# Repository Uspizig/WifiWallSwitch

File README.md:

A WallSwitch with a clever EINK Display that measures your Air Quality, measures Temperature, detects movement, measures Light Conditions... and many more.
And the Best of all: "It can be your own LOCAL Voice Assistant or MediaPlayer"

This Device perfectly integrates in your Smart Home (e.g. HomeAssistant or IO Broker).  
No permanent backlight On Display that disturbs your sleep. Just a brillant E-Ink Display with outstanding contrast and some Buttons that you can feel when you swipe over with your plam.
A lightweight Design with a perfect WAF Factor. Fits on your Desktop or on your wall. 
The device can be programmed, adapted, hacked, tinkered and individualised by YOU.
You want to push boundries even further: Use Arduino and do a deep Dive in Ultra Low Power Mode. The Battery might run for Years with an intelligent Power Gateing.

Eight Ambient Light LEDs can give you a visual quick feedback if needed:

View of the components in HomeAssistant

What is under the hood:
Main thing you see when you have a first look is the massive 2.7 " E-Ink Screen

See it in Action here: https://twitter.com/USpizig/status/1747731234338336940

Hardware Specs:
- 2.7" EInk Epaper with or without Touch Screen... other screens might work as well
- ESP32 S3 Dual Core Microcontroller with USB OTG, Wifi & BT, Mass Storage Mode. 
- 8 X SK6812 Mini RBG LEDs
- 8 X Hardware Buttons...REAL BUTTONS with clicks: No Touch Buttons that might not work if you have wet or dirty fingers
- BOSCH BME680 for eCo2, Temperature, Humidity and Pressure Measurements
- ST LSM6DSL Ultra Low Noise MEMS Gyro + Accel for Movement Detection and Earthquake Detection
- INMP441 MEMS Microphone for Voice Assistant
- Socket for MAX98357A I2S Class D Amplifier for Audio Output for Media Player
- LDR Ambient Light Sensor: Detect the Ambient Light conditions in your room.
- RTC1: TPL5110 for PowerGateing and low Standby Current
- RTC2 Option: RV3028 C7 for Ultra Low RTC with Backup Cap lasts 3h
- Optional: RFM95 LoRa Radio for Desaster Radio (Limitations: May not work together with Microphone)
- Connector for KNX EIB Smart Home with Nano BCU
- Connector for Your Own Ideas... Several free GPIOs
- Switch for adapting to Waveshare/Gooddisplay EINK Display
- All SMD components have a size 0603 or larger to enable easier soldering/Tinkering.

Underneath the EINK Screen is a placeholder for an optional RFM95/RFM98 Long Range Communication Module. This Module works with LoRa, FSK or other wireless standards. 
Up 15km Range of communication can be established with this module. Perfect as well for decoding your Bresser Weather Station and translate it to MQTT for your Smart Home.

The other side of the PCB looks like this:

If you scroll further down you may see a picture of the TOP View of the PCB
On the Top side of the PCB you see the Main Processor: This is an ESP32-S3 and various sensors:
- Ultra Low Power RTC RV3028 [U9] for Low Power Battery Operation wakeup
- Ultra Low Noise MEMS LSM6DSL [U8] 6 Axis GYRO+ACCEL + Tap Detection
- Ultra Low Power Gateing Chip TPL5110: [U6]
- Bosch BME680 for Air Quality Measurements [U5]
- EInk Screen connector 
- Touch Screen connector [JP5]
- Space for the oprional INMP441 Microphone [J5], [J9]
- 8 RGB LEDs which can be adressed individually. Perfect for Quizshow effects. Ideal for Audiovisual feeddback
- 9 Click Buttons. [SW1-SW9] - SW5 is hidden under the screen and can be used as Physical Click Button
- Space for Several Connectors[J2, J8, J3] to plugin even more modules like Audio Module for an Media Player or Voice Assistant Feedback.

And another view with all the SMD Parts simulated:

What is currently working:

Hardware:
- Currently the HW BringUp is about to finish.
- The basic Hardware is up and running stable.
- Eink, Microphone, LEDs, Buttons, BME680. LSM6 Gyro work well.

The optional Modules are  still under test
  -   TP4065 Lipo Battery Charger Circuit
  -   Battery Switchover Circuit once Battery is fully charged to avoid Battery damage due to overcharging
  -   TPL5110 Low Power RTC Module
  -   RV3028 Low Power Module
  -   Long Range Communication Module RF Module RFM95
  -   230V Power Converter to 5V/3.3V for Wall Mode.

Software Sketches working:
Arduino:
  - Flashing the Device over USB with you Chrome Web Browser: https://web.esphome.io/
  - Logging over USB USBSerial
  - EInk Basic Update of content
  - EInk Partial Update Dynamic Update of content
  - Read out BME680 Data (Temp, Humidity, Pressure, eCO2, IAQ,...)
  - Microfone: Calculate loudness in dBA
  - Audio Player: Playback MP3, TTS via Google and Webradio
  - 8 Buttons can be detected.
  - 8 RGB LEDS whcih can be adressed individually
  - LSM6 Gyro: Read out of Basic Values Roll, Pitch, Yaw
  - All typical 24pin EInk Displays which are mentioned on GxEPD2: https://github.com/ZinggJM/GxEPD2/tree/master
  - Flashing & Logging the Device over 2.54mm Socket with a dedicated Flash Adapter

 Home Assistant with ESPHome Integration:
   - Flashing the Device over USB with you Chrome Web Browser: https://web.esphome.io/
   - Logging over USB with ESP Home
   - Display Messages on EInk Display
   - Voice Assistant: Switch on Light,.... you name it
   - Media Player: Playback of TTS Messages, Audio Files,Web Radio
   - Keyboard: 8 Buttons are detected individulally
   - RGB LED Control SK6812 Mini
   - Flashing & Logging the Device over 2.54mm Socket with a dedicated Flash Adapter
     
Known ESPHome Issues right now:
  - Voice Assistant has some issues if used together with Media Player. Leads to Stuttering Audio once Media Playback is started.
  - No LSM GYRO integration
  - 2 GPIOS used to much due to Keypad component of ESPhome only supports 4x4 Matrix Keyboards
  - GPIO8 can not be used for Keyboard Fake Keys.

Known Issues on Arduino:
  - LSM6 Gyro has some issues with BME680 BSEC: Leads to constant output of 500 ppm

What is planned:
- EInk Touch Screen 2.7 'integration of Good Display https://www.good-display.com/product/259.html
- A Touch screen https://www.good-display.com/product/259.html
- Read out data of a Weather Station Bresser 6in1 We<ther Station and forward to MQTT with an RFM95 Chip.
- LDR for Light Detection. Monitoring of Enviroment Data
- Ultra Low Power RTC RV3028 for Low Power Battery Operation wakeup
- Ultra Low Noise MEMS LSM6DSL GYRO+ACCEL for Earthquake Detection-> https://github.com/biagiom/QuakeSense
- Ultra Low Noise MEMS LSM6DSL for movement detection and Tap Detection
- Ultra Low Power Mode TPL5110: Let the Processor sleep with TPL5110 Power Gateing and shut down all that is battery draining.
- Bosch BME680 for Air Quality Measurements
- 9 physical buttons for moments where you do not wnat to use a touchscreen
- KNX Integraion with Nano BCU
- LORA:
  - Transmit Air Quality Data on a regular Basis (every 15min)
  - Transmit Data when Air Quality changes dramatically
  - Transmit Data when Air Quality changes dramatically
  - Recieve Commands to Switch on / off ext Relay
  - Switch to Desaster Mode and search for BLE Heart Rate Devices nearby and sent this data via LoRa

WARNINGS
This is my hobby. Please do NOT be a DIRTY COPY CAT and make your own comercial product out of it.
See License before you copy anything out of it.
 
If you use this Hardware, Software, Code or schematics you agree that any harm, damage, burn or injuries are YOUR RESPONSIBILITY! 
The Author may not be held liable for any damage that might happen if you try this code out or use this product or parts of it.
Legal validity of this disclaimer: This disclaimer is to be regarded as part of the internet publication which you were referred from. 
If sections or individual terms of this statement are not legal or correct, the content or validity of the other parts remain uninfluenced by this fact.

Referrals and links The author is not responsible for any contents linked or referred to from his pages - unless he has full knowledge of illegal contents and would be able to prevent the visitors of his site from viewing those pages. If any damage occurs by the use of information presented there, the author might not be liable. Furthermore the author is not liable for any postings or messages published by users of discussion boards, guest books or mailing lists provided.

Arduino:
Before you compile please ensure you modify all your credentials and used sensors in "credentials.h" which have been marked REPLACEMEUSER
This Source Code is provided "AS it is" . 
Also ensure you have installed the following libs:
Code Sources that influenced this Source Code and which libaries you may need:

https://github.com/knolleary/pubsubclient/blob/master/examples/mqtt_auth/mqtt_auth.ino
https://randomnerdtutorials.com/esp32-mqtt-publish-subscribe-arduino-ide/
RGBW for SK6812:
Original code by Jim Bumgardner (http://krazydad.com).
Modified by David Madison (http://partsnotincluded.com).
Extended by Christoph Wempe
https://gist.github.com/CWempe?direction=desc&sort=created

Adafruit BME/BMP280/SGP30 sketches/libs
Please consider buying their products due to their great work in Arduino libs
https://github.com/adafruit/Adafruit_SGP30
https://github.com/adafruit/Adafruit_BMP280_Library

Bosch BME680 BSEC Lib
https://github.com/BoschSensortec/BSEC-Arduino-library

Andreas Spiess
OTA Sketch for OTA Update of the ESP32 over Wifi
https://github.com/SensorsIot/ESP32-OTA

Knolleary pubsubclient
/pubsubclient/blob/master/examples/mqtt_auth/mqtt_auth
https://github.com/knolleary/pubsubclient

Fastled
https://github.com/FastLED/FastLED

Settings for Jumpers & Solder Bridges:
Jumper:
- JP2 = This MUST BE OPEN! if USB Connected & 3.3V Prog
- JP3 = GYRO INT Emergency CUT: If you want no more Interupts from the Gyro.
- JP4 = MAINS Mode / No TPL5110 Mode. Disable the RTC for Power Gateing. Use for permanent connection to USB
- JP5 = RV3028 INT CUT for RFM95 OP. Must be cut if an RFM Long Range RF Mode is installed
- JP6 = Switch of Input Power Supply Voltage
- JP5 = Solder for RFM95 OP & Cut JP5

I²C Address of onboard Devices.
- 0x52 RV3028
- 0x6A LSM6DSL
- 0x77 BME680

Testpoints for soldering and Tinkering:
TP1 EPD VCOM -> Debuging of EINK
TP2 CLK RV3028 
TP3 INT RV3028
TP4 EPD PREVGL -> Debuging of EINK
TP5 EPD PREVGH -> Debuging of EINK
TP6 TPL DNE -> Debuging of EINK... Connect to a GPIO for Ulatra Low Power sleep and fire a 1 whenever you want to Deep Sleep on that GPIO
TP7 SHOT RV3028 -> Wakeup Pin for RTC2
TP8 RFM CS -> Soldering Pin needed for RFM95
TP9 JTAG/Done
TP10 RFM ANT -> Connector for 868 MHZ Antenna
TP11 TPL SHOT -> Wakeup Pin for TPL 5110 RTC
TP12 GYRO INT2
TP13 GYRO INT1
TP14 TOUCH RES -> Touch Controller Reset Pin. Hopefully never needed
TP15 BAT CHRG -> Battery charg Pin. Hopefully never needed.

Known HW Limitations:
- LDR is not working when WIFI is ON. Stupid ESP32-S3 Limitations ADC2 is not working if WIFi is on
- HW Buttons placed 90° wrong. Wrong Pinout matching

TODO:
- RV_3028 INT ist connected with LORA RFM MISO. No paralell usage possible
- INMP441 Mic ist connected with LORA RFM95. No paralell usage possible
- USB ESD Diodes missing
- SK6812 is an input of KNX connector at the same time?
- Rerouting of SK6812 necesssary. Not possible to  GPIO 0... otherwise board will not start.
- Done Pin TPL5110 not routed to ESP32 IO3. No Power Shutdown without a Solder Bridge
-

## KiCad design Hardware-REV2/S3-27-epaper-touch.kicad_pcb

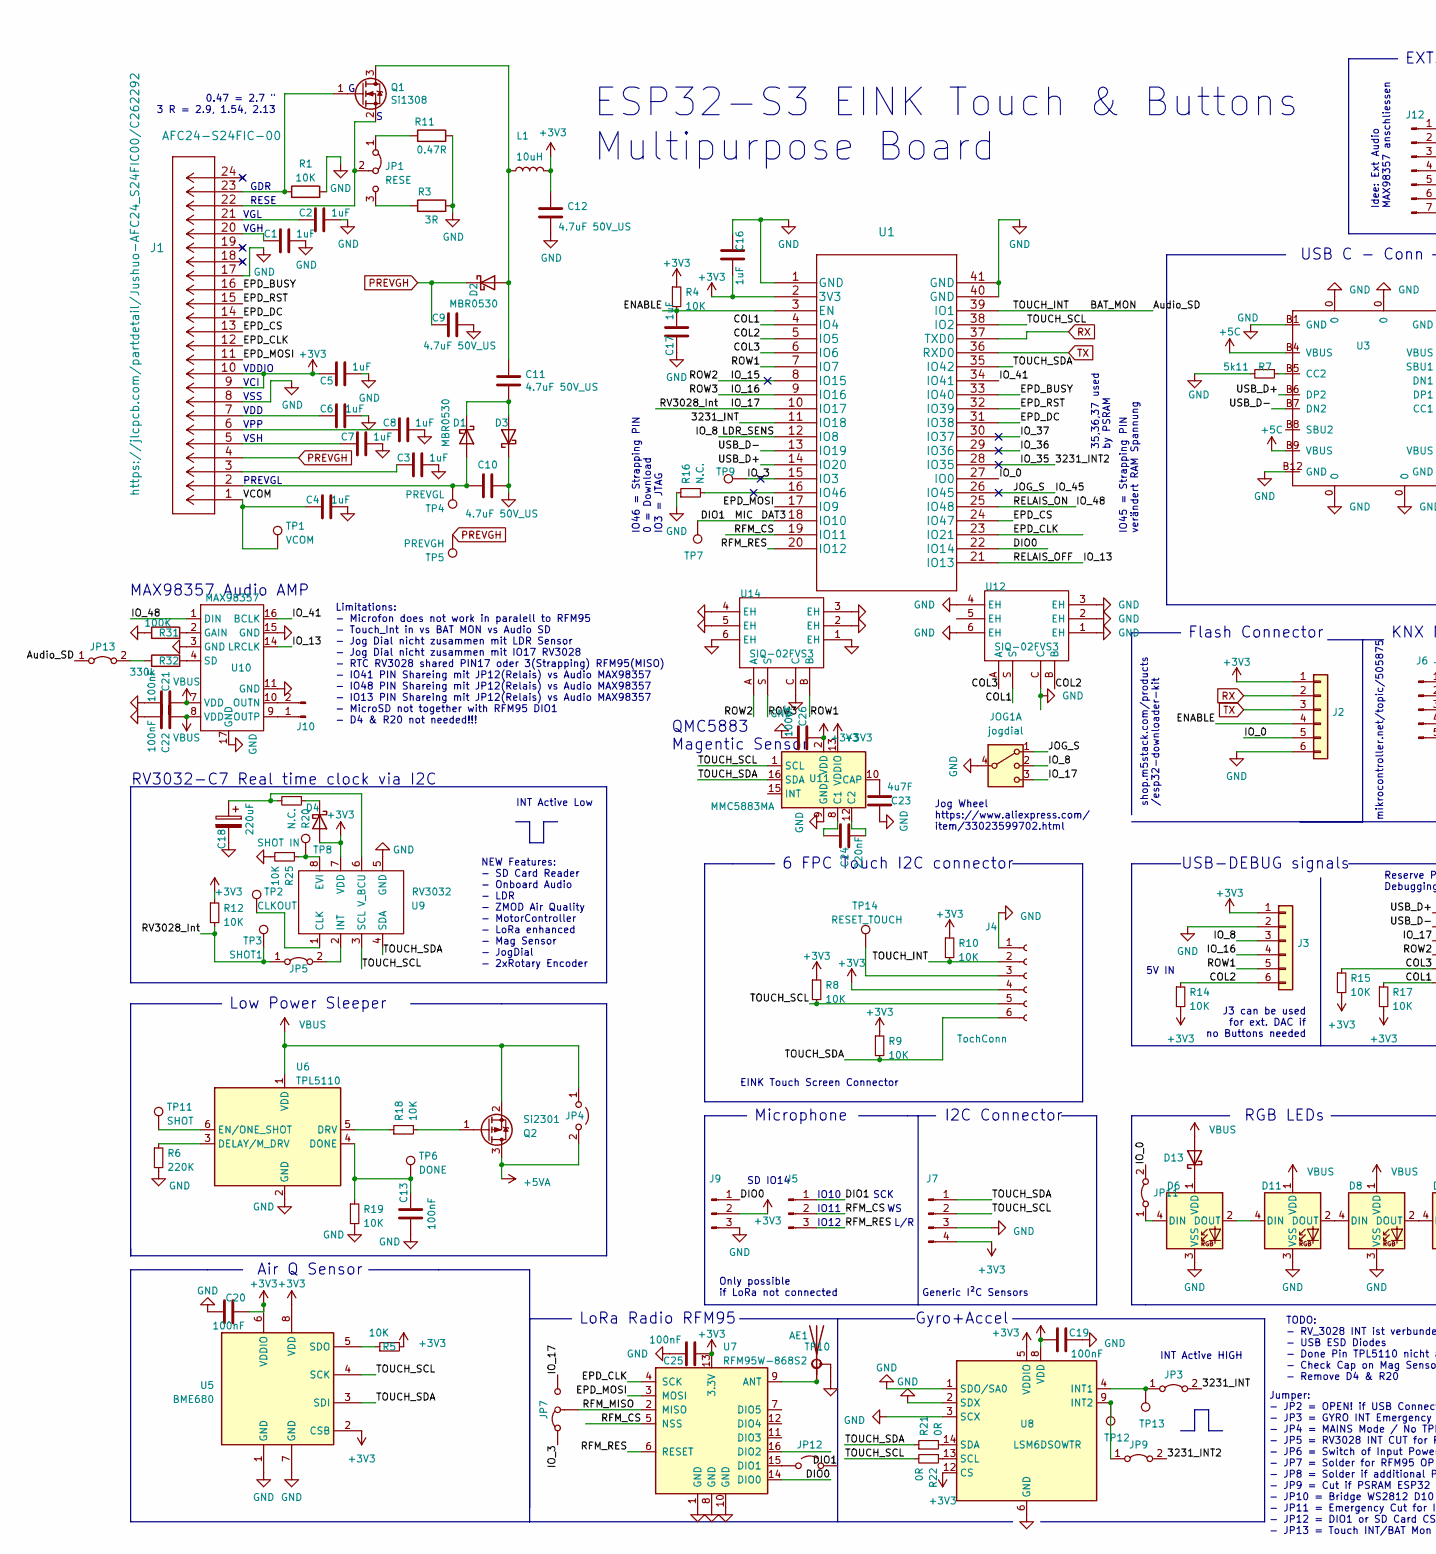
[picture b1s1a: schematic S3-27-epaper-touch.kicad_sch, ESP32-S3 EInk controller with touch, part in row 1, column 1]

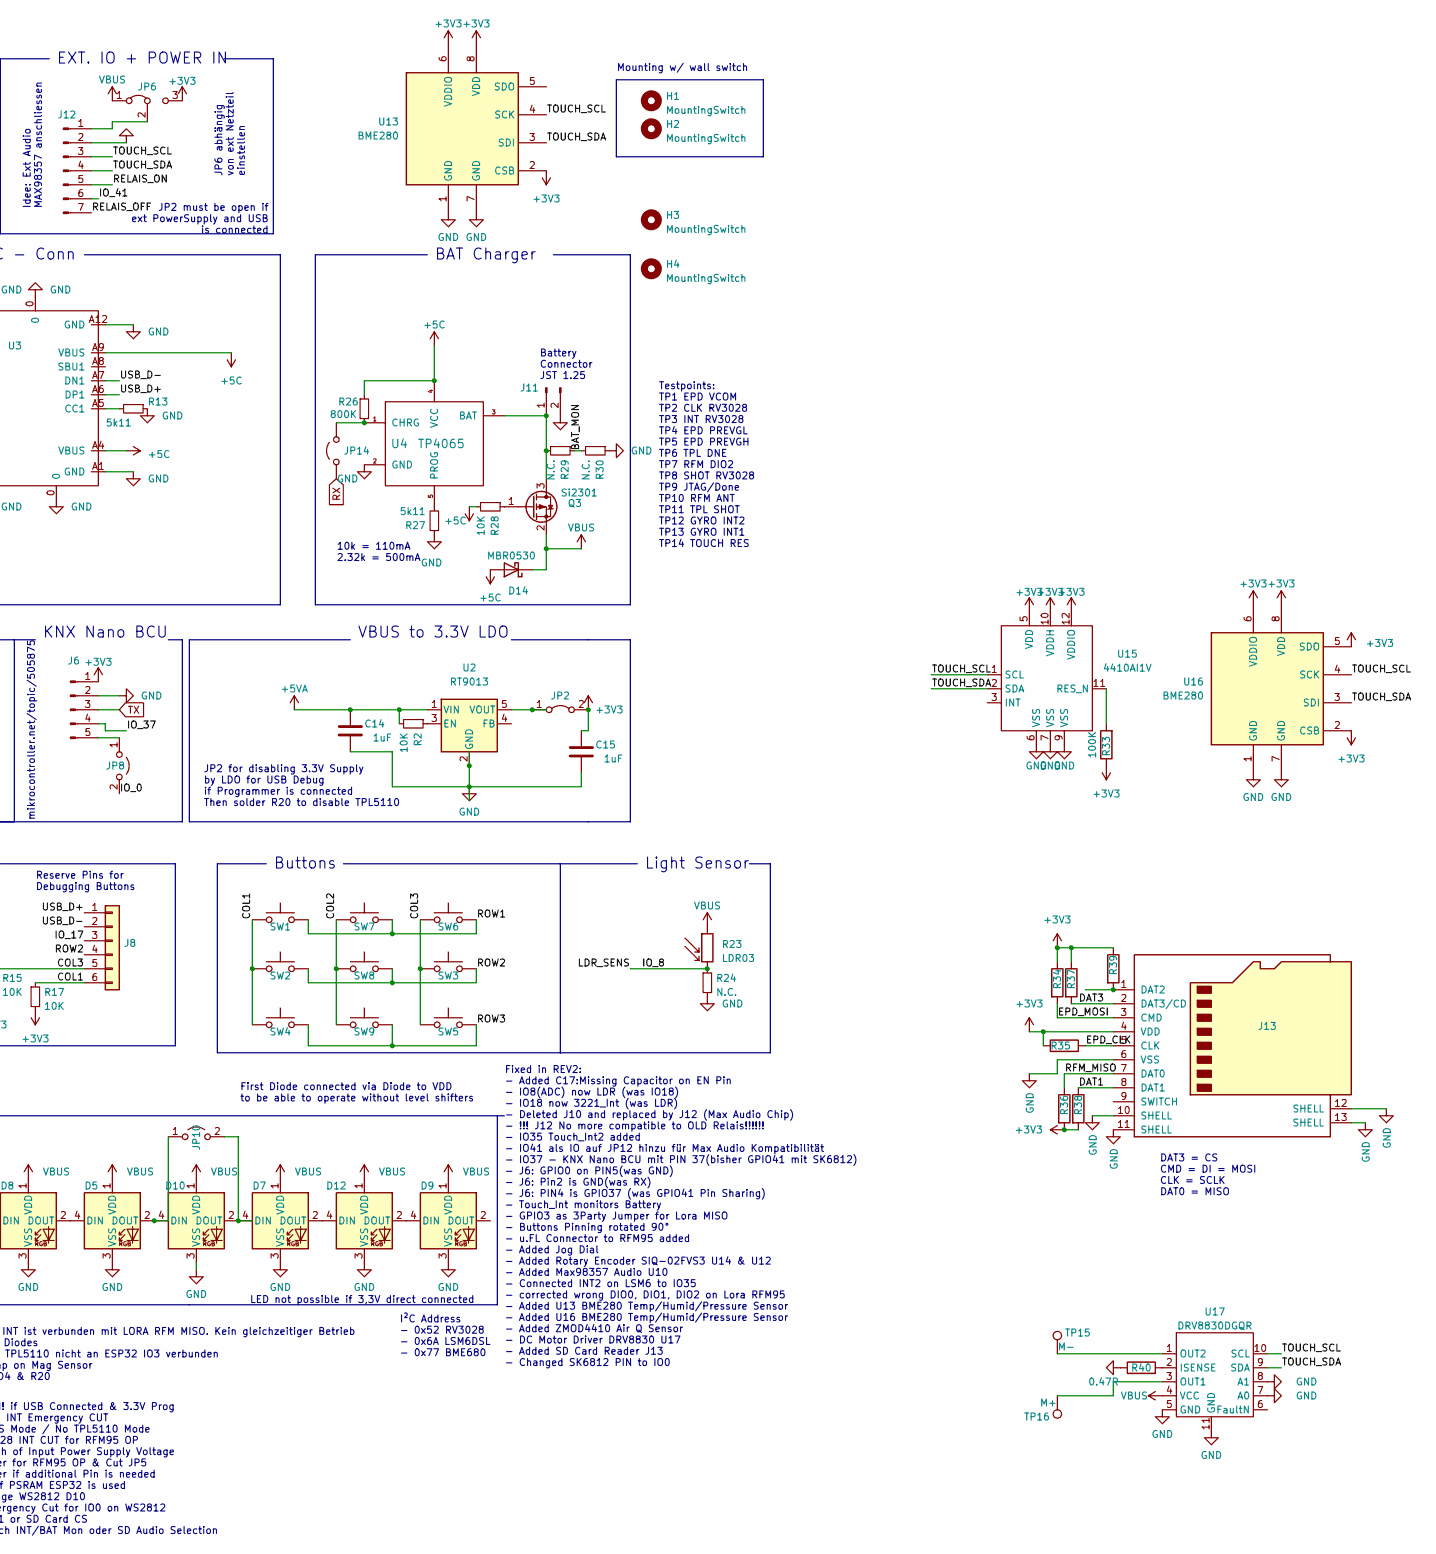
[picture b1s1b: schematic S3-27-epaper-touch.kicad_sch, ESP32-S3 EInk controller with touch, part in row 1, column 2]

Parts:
AE1: Antenna_Shield; U.FL_Molex_MCRF_73412-0110_Vertical
C1, C2, C3, C4, C5, C6, C7, C8, C14, C15, C16, C17: 1uF; C_0805_2012Metric_Pad1.18x1.45mm_HandSolder; LCSC C28323
C9, C10, C11, C12: 4.7uF 50V_US; C_0805_2012Metric_Pad1.18x1.45mm_HandSolder; LCSC C162420
C13, C19, C20: 100nF; C_0805_2012Metric_Pad1.18x1.45mm_HandSolder; LCSC C49678
C18: 220uF; CP_EIA-3528-21_Kemet-B
C21, C22, C26: 100nF; C_0805_2012Metric_Pad1.18x1.45mm_HandSolder
C23: 4u7F; C_0805_2012Metric_Pad1.18x1.45mm_HandSolder
C24: 220nF; C_0805_2012Metric_Pad1.18x1.45mm_HandSolder
C25: 100nF; C_0603_1608Metric_Pad1.08x0.95mm_HandSolder
D1, D2, D3, D4, D13, D14: MBR0530; D_SOD-123
D5, D6, D7, D8, D9, D10, D11, D12: SK6812MINI-E; MX_SK6812MINI-E
H1, H2: MountingSwitch; MountingHole_3.2mm_M3
H3, H4: MountingSwitch; baerklein
J1: AFC24-S24FIC-00; FPC-SMD_P0.50-24P_QCHF-SM-H2.0; LCSC C262292
J2, J3, J8: Conn_01x06; PinHeader_1x06_P2.54mm_Vertical
J4: TochConn; FFC-SMD_6P-P0.50_FH34SRJ-6S-0.5SH; LCSC C224194
J5, J9: Conn_01x03_Pin; PinHeader_1x03_P2.54mm_Vertical
J6: Conn_01x05_Pin; PinHeader_1x05_P2.54mm_Vertical
J7: Conn_01x04_Pin; PinHeader_1x04_P2.54mm_Vertical
J10: Conn_01x02_Pin; PinHeader_1x02_P2.00mm_Vertical
J11: Conn_01x02_Pin; JST_GH_SM02B-GHS-TB_1x02-1MP_P1.25mm_Horizontal
J12: Conn_01x07_Pin; PinHeader_1x07_P2.54mm_Vertical
J13: Micro_SD_Card_Det_US; TF-SMD_XKTF-0803-0
JOG1: jogdial; JogWheel
JP1: RESE; SW-SMD_G-SWITCH_MK-12C02-G015; LCSC C2911519
JP2, JP3, JP5, JP11: Jumper_2_Bridged; SolderJumper-2_P1.3mm_Bridged_RoundedPad1.0x1.5mm
JP4, JP8, JP12, JP14: Jumper_2_Open; SolderJumper-2_P1.3mm_Open_RoundedPad1.0x1.5mm
JP6, JP7: Jumper_3_Bridged12; SolderJumper-3_P1.3mm_Bridged12_RoundedPad1.0x1.5mm_NumberL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
JP9, JP13: Jumper_2_Bridged; SolderJumper-2_P1.3mm_Open_RoundedPad1.0x1.5mm
JP10: Jumper_2_Open; SolderJumper-2_P1.3mm_Bridged_RoundedPad1.0x1.5mm
L1: 10uH; IND-SMD_L4.0-W4.0
Q1: Si1308; SOT-323_SC-70
Q2, Q3: Si2301; SOT-23
R1, R2, R4, R5, R8, R9, R10, R12, R14, R15, R17, R18, R19, R25, R28: 10K; R_0805_2012Metric_Pad1.20x1.40mm_HandSolder; LCSC C17414
R3: 3R; R_0805_2012Metric_Pad1.20x1.40mm_HandSolder
R6: 220K; R_0805_2012Metric_Pad1.20x1.40mm_HandSolder
R7, R13, R27: 5k11; R_0805_2012Metric_Pad1.20x1.40mm_HandSolder; LCSC C27834
R11, R40: 0.47R; R_0805_2012Metric_Pad1.20x1.40mm_HandSolder
R16, R24, R29, R30: N.C.; R_0603_1608Metric_Pad0.98x0.95mm_HandSolder
R20: N.C.; R_0805_2012Metric_Pad1.20x1.40mm_HandSolder
R21, R22: 0R; R_0805_2012Metric_Pad1.20x1.40mm_HandSolder; LCSC C17477
R23: LDR03; R_LDR_10x8.5mm_P7.6mm_Vertical
R26: 800K; R_0805_2012Metric_Pad1.20x1.40mm_HandSolder
R31: 100K; R_0805_2012Metric_Pad1.20x1.40mm_HandSolder
R32: 330k; R_0805_2012Metric_Pad1.20x1.40mm_HandSolder
R33: 100K; R_0603_1608Metric_Pad0.98x0.95mm_HandSolder
R34, R35, R36, R37, R38, R39: 10k; R_0603_1608Metric_Pad0.98x0.95mm_HandSolder
SW1, SW2, SW3, SW4, SW5, SW6, SW7, SW8, SW9: SW_Push; SW-SMD_4P-CORR-L5.2-W5.2-P3.70-LS6.4
TP1, TP7, TP9, TP13: VCOM; TestPoint_Pad_D1.5mm
TP2: CLKOUT; TestPoint_Pad_D1.5mm
TP3: SHOT1; TestPoint_Pad_D1.5mm
TP4: PREVGL; TestPoint_Pad_D1.5mm
TP5: PREVGH; TestPoint_Pad_D1.5mm
TP6: DONE; TestPoint_Pad_D1.5mm
TP8: SHOT IN; TestPoint_Pad_D1.5mm
TP10: VCOM; PinHeader_1x01_P2.54mm_Vertical
TP11: SHOT; TestPoint_Pad_D1.5mm
TP12: VCOM; TestPoint_Pad_D1.0mm
TP14: RESET_TOUCH; TestPoint_Pad_D1.5mm
TP15: M-; TestPoint_Pad_D1.0mm
TP16: M+; TestPoint_Pad_D1.0mm
U1: ESP32-S3-WROOM-1-N8; ESP32-S3-WROOM-1
U2: RT9013; SOT-23-5; LCSC C47773
U3: KoreanHropartsElecTYPE-C-31-M-12; USB-C_SMD-TYPE-C-31-M-12; LCSC C165948
U4: TP4065; SOT-23-5_L3.0-W1.7-P0.95-LS2.8-BR; LCSC C113540
U5: BME680; LGA-8_L3.0-W3.0-P0.80-TR; LCSC C125972
U6: TPL5110; SOT-23-6; LCSC C125830
U7: RFM95W-868S2; HOPERF_RFM9XW_SMD; LCSC C2844472
U8: LSM6DSOWTR; LGA-14_3x2.5mm_P0.5mm_LayoutBorder3x4y; LCSC C2829074
U9: RV3032; rv3028
U10: MAX98357; TQFN-16_L3.0-W3.0-P0.50-BL-EP1.5
U11: MMC5883MA; LGA-16_3x3mm_P0.5mm
U12, U14: SIQ-02FVS3; SW-SMD_SIQ-02FVS3_1; Manufacturer Part SIQ-02FVS3; LCSC Part Name 拨轮滚轮旋转编码器开关
U13, U16: BME280; Bosch_LGA-8_2.5x2.5mm_P0.65mm_ClockwisePinNumbering
U15: 4410AI1V; ZMOD4410AI1V
U17: DRV8830DGQR; HVSSOP-10-1EP_3x3mm_P0.5mm_EP1.57x1.88mm

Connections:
+3V3: C5.2, C12.2, C15.1, C16.1, C19.2, C20.2, C25.2, C26.1, D4.2 (A), J1.9, J1.10, J2.1, J3.1, J4.4, J6.1, J7.4, J9.2, J13.4 (VDD), JP2.2 (B), JP6.3 (B), L1.2, R4.1, R5.2, R8.1, R9.1, R10.1, R12.1, R14.2, R15.2, R17.2, R33.1, R34.1, R35.1, R36.2, R37.1, R38.2, R39.1, U1.2 (3V3), U5.2 (CSB), U5.6 (VDDIO), U5.8 (VDD), U7.13 (3.3V), U8.5 (VDDIO), U8.8 (VDD), U8.12 (CS), U9.7 (VDD), U11.2 (VDD), U11.13 (VDDIO), U13.2 (CSB), U13.6 (VDDIO), U13.8 (VDD), U15.5 (VDD), U15.10 (VDDH), U15.12 (VDDIO), U16.2 (CSB), U16.5 (SDO), U16.6 (VDDIO), U16.8 (VDD)
+5C: D14.2 (A), R26.1, R28.2, U3.A4 (VBUS), U3.A9 (VBUS), U3.B4 (VBUS), U3.B9 (VBUS), U4.4 (VCC)
+5VA: C14.1, JP4.2 (B), Q2.3 (D), R2.2, U2.1 (VIN)
/3231_INT: JP3.2 (B), U1.11 (IO18)
/3231_INT2: JP9.2 (B), U1.28 (IO35)
/Audio_SD: J4.2, JP13.1 (A), R10.2, R29.1, R30.2, U1.39 (IO1)
/COL1: J8.6, R17.1, SW1.1, SW2.1, SW4.1, U1.4 (IO4), U12.S
/COL2: J3.6, R14.1, SW7.1, SW8.1, SW9.1, U1.5 (IO5), U12.B
/COL3: J8.5, R15.1, SW3.1, SW5.1, SW6.1, U1.6 (IO6), U12.A
/DAT1: J13.8 (DAT1), R38.1
/DAT3: J5.1, J13.2 (DAT3/CD), JP12.2 (B), R37.2, TP7.1, U1.18 (IO10)
/DIO0: J9.1, U1.22 (IO14), U7.14 (DIO0)
/ENABLE: C17.1, J2.4, R4.2, U1.3 (EN)
/EPD_BUSY: J1.16, U1.33 (IO40)
/EPD_CLK: J1.12, J13.5 (CLK), R35.2, U1.23 (IO21), U7.4 (SCK)
/EPD_CS: J1.13, U1.24 (IO47)
/EPD_DC: J1.14, U1.31 (IO38)
/EPD_MOSI: J1.11, J13.3 (CMD), R34.2, U1.17 (IO9), U7.3 (MOSI)
/EPD_RST: J1.15, U1.32 (IO39)
/IO_0: J2.5, JP8.2 (B), JP11.2 (B), U1.27 (IO0)
/IO_3: JP7.1 (A), TP9.1, U1.15 (IO3)
/IO_8: J3.3, JOG1.2, R23.2, R24.1, U1.12 (IO8); also elsewhere on the board
/IO_13: J12.7, U1.21 (IO13), U10.14 (LRCLK)
/IO_15: J8.4, SW2.2, SW3.2, SW8.2, U1.8 (IO15), U14.A
/IO_16: J3.4, SW4.2, SW5.2, SW9.2, U1.9 (IO16), U14.S
/IO_17: J8.3, JOG1.3, JP5.1 (A), JP7.3 (B), R12.2, TP3.1, U1.10 (IO17); also elsewhere on the board
/IO_36: U1.29 (IO36)
/IO_37: J6.4, U1.30 (IO37)
/IO_41: J12.6, U1.34 (IO41), U10.16 (BCLK)
/IO_45: JOG1.1, U1.26 (IO45); also elsewhere on the board
/IO_48: J12.5, U1.25 (IO48), U10.1 (DIN)
/RFM_CS: J5.2, U1.19 (IO11), U7.5 (NSS)
/RFM_MISO: J13.7 (DAT0), JP7.2 (C), R36.1, U7.2 (MISO)
/RFM_RES: J5.3, U1.20 (IO12), U7.6 (RESET)
/ROW1: J3.5, SW1.2, SW6.2, SW7.2, U1.7 (IO7), U14.B
/TOUCH_SCL: J4.5, J7.2, J12.3, R8.2, R22.2, U1.38 (IO2), U5.4 (SCK), U9.3 (SCL), U11.1 (SCL), U13.4 (SCK), U15.1 (SCL), U16.4 (SCK), U17.10 (SCL)
/TOUCH_SDA: J4.6, J7.1, J12.4, R9.2, R21.1, U1.35 (IO42), U5.3 (SDI), U9.4 (SDA), U11.16 (SDA), U13.3 (SDI), U15.2 (SDA), U16.3 (SDI), U17.9 (SDA)
/USB_D+: J8.1, U1.14 (IO20), U3.A6 (DP1), U3.B6 (DP2)
/USB_D-: J8.2, U1.13 (IO19), U3.A7 (DN1), U3.B7 (DN2)
/VCOM: C4.2, J1.1, TP1.1
GND: AE1.2 (Shield), C1.1, C2.1, C3.1, C4.1, C5.1, C6.1, C7.1, C8.1, C9.1, C10.1, C12.1, C13.2, C14.2, C15.2, C16.2, C17.2, C18.2, C19.1, C20.1, C21.2, C22.2, C23.1, C25.1, C26.2, D3.1 (K), D5.3 (VSS), D6.3 (VSS), D7.3 (VSS), D8.3 (VSS), D9.3 (VSS), D10.3 (VSS), D11.3 (VSS), D12.3 (VSS), J1.8, J1.17, J2.6, J3.2, J4.1, J6.2, J7.3, J9.3, J11.2, J12.2, J13.6 (VSS), J13.10 (SHELL), J13.11 (SHELL), J13.12 (SHELL), J13.13 (SHELL), JOG1.4, R1.2, R3.2, R6.2, R7.2, R11.2, R13.1, R16.1, R19.2, R24.2, R25.2, R27.1, R30.1, R31.1, R40.1, U1.1 (GND), U1.40 (GND), U1.41 (GND), U2.2 (GND), U3.0, U3.A1 (GND), U3.A12 (GND), U3.B1 (GND), U3.B12 (GND), U4.2 (GND), U5.1 (GND), U5.7 (GND), U6.2 (GND), U7.1 (GND), U7.8 (GND), U7.10 (GND), U8.1 (SDO/SA0), U8.2 (SDX), U8.3 (SCX), U8.6 (GND), U8.7 (GND), U9.5 (GND), U10.3 (GND), U10.11 (GND), U10.15 (GND), U10.17 (GND), U11.9 (GND), U11.11 (GND), U12.1 (EH), U12.2 (EH), U12.3 (EH), U12.4 (EH), U12.6 (EH), U12.C, U13.1 (GND), U13.7 (GND), U14.1 (EH), U14.2 (EH), U14.3 (EH), U14.4 (EH), U14.5 (EH), U14.6 (EH), U14.C, U15.6 (VSS), U15.7 (VSS), U15.9 (VSS), U16.1 (GND), U16.7 (GND), U17.5 (GND), U17.7 (A0), U17.8 (A1), U17.11 (GND); also elsewhere on the board
unnamed: AE1.1 (A), TP10.1, U7.9 (ANT)
unnamed: C1.2, J1.20
unnamed: C2.2, J1.21
unnamed: C3.2, J1.3
unnamed: C6.2, J1.7
unnamed: C7.2, J1.5
unnamed: C8.2, J1.6
unnamed: C10.2, D1.2 (A), J1.2, TP4.1
unnamed: C11.1, D1.1 (K), D3.2 (A)
unnamed: C11.2, D2.2 (A), L1.1, Q1.3 (D)
unnamed: D4.1 (K), R20.1
unnamed: D5.4 (DIN), D8.2 (DOUT)
unnamed: D6.4 (DIN), JP11.1 (A)
unnamed: D5.2 (DOUT), D10.4 (DIN), JP10.1 (A)
unnamed: D7.4 (DIN), D10.2 (DOUT), JP10.2 (B)
unnamed: D6.2 (DOUT), D11.4 (DIN)
unnamed: D8.4 (DIN), D11.2 (DOUT)
unnamed: D7.2 (DOUT), D12.4 (DIN)
unnamed: D9.4 (DIN), D12.2 (DOUT)
unnamed: D6.1 (VDD), D13.1 (K)
unnamed: J4.3, TP14.1
unnamed: J6.5, JP8.1 (A)
unnamed: J10.1, U10.9 (OUTP)
unnamed: J10.2, U10.10 (OUTN)
unnamed: J11.1, Q3.3 (D), R29.2, U4.3 (BAT)
unnamed: J12.1, JP6.2 (C)
unnamed: J13.1 (DAT2), R39.2
unnamed: JP1.1 (A), R11.1
unnamed: JP1.3 (B), R3.1
unnamed: J1.22, JP1.2 (C), Q1.2 (S)
unnamed: JP2.1 (A), U2.5 (VOUT)
unnamed: JP3.1 (A), TP13.1, U8.4 (INT1)
unnamed: JP5.2 (B), U9.2 (INT)
unnamed: JP9.1 (A), TP12.1, U8.9 (INT2)
unnamed: JP12.1 (A), U7.15 (DIO1)
unnamed: JP13.2 (B), R32.1
unnamed: JP14.2 (B), R26.2, U4.1 (CHRG)
unnamed: J1.23, Q1.1 (G), R1.1
unnamed: Q2.1 (G), R18.2
unnamed: Q3.1 (G), R28.1
unnamed: R16.2, U1.16 (IO46)
unnamed: R2.1, U2.3 (EN)
unnamed: R13.2, U3.A5 (CC1)
unnamed: R7.1, U3.B5 (CC2)
unnamed: R27.2, U4.5 (PROG)
unnamed: R5.1, U5.5 (SDO)
unnamed: R6.1, U6.3 (DELAY/M_DRV)
unnamed: C13.1, R19.1, TP6.1, U6.4 (DONE)
unnamed: R18.1, U6.5 (DRV)
unnamed: TP11.1, U6.6 (EN/ONE_SHOT)
unnamed: R22.1, U8.13 (SCL)
unnamed: R21.2, U8.14 (SDA)
unnamed: TP2.1, U9.1 (CLK)
unnamed: R25.1, TP8.1, U9.8 (EVI)
unnamed: C18.1, R20.2, U9.6 (V_BCU)
unnamed: R31.2, U10.2 (GAIN)
unnamed: R32.2, U10.4 (SD)
unnamed: C24.1, U11.8 (C1)
unnamed: C24.2, U11.12 (C2)
unnamed: C23.2, U11.10 (CAP)
unnamed: R33.2, U15.11 (RES_N)
unnamed: R40.2, U17.2 (ISENSE)
unnamed: TP16.1, U17.3 (OUT1)
unnamed: TP15.1, U17.1 (OUT2)
PREVGH: C9.2, D2.1 (K), J1.4, TP5.1
RX: J2.2, JP14.1 (A), U1.37 (TXD0)
TX: J2.3, J6.3, U1.36 (RXD0)
VBUS: C21.1, C22.1, D5.1 (VDD), D7.1 (VDD), D8.1 (VDD), D9.1 (VDD), D10.1 (VDD), D11.1 (VDD), D12.1 (VDD), D13.2 (A), D14.1 (K), JP4.1 (A), JP6.1 (A), Q2.2 (S), Q3.2 (S), R23.1, U6.1 (VDD), U10.7 (VDD), U10.8 (VDD), U17.4 (VCC)

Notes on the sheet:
PREVGL
Gyro+Accel
Limitations: - Microfon does not work in paralell to RFM95 - Touch_Int in vs BAT MON vs Audio SD - Jog Dial nicht zusammen mit LDR Sensor - Jog Dial nicht zusammen mit IO17 RV3028 - RTC RV3028 shared PIN17 oder 3(Strapping) RFM95(MISO) - IO41 PIN Shareing mit JP12(Relais) vs Audio MAX98357 - IO48 P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
EXT. IO + POWER IN
RESE
VCI
Testpoints: TP1 EPD VCOM TP2 CLK RV3028 TP3 INT RV3028 TP4 EPD PREVGL TP5 EPD PREVGH TP6 TPL DNE TP7 RFM DIO2 TP8 SHOT RV3028 TP9 JTAG/Done TP10 RFM ANT TP11 TPL SHOT TP12 GYRO INT2 TP13 GYRO INT1 TP14 TOUCH RES
VDDIO
shop.m5stack.com/products /esp32-downloader-kit
IO11
SD IO14
USB-DEBUG signals
JP2 for disabling 3.3V Supply by LDO for USB Debug if Programmer is connected Then solder R20 to disable TPL5110
Microphone
QMC5883 Magentic Sensor
Low Power Sleeper
LED not possible if 3,3V direct connected
MAX98357 Audio AMP
0.47 = 2.7 " 3 R = 2.9, 1.54, 2.13
DAT3 = CS CMD = DI = MOSI CLK = SCLK DAT0 = MISO
RV3032-C7 Real time clock via I2C
35,36,37 used by PSRAM
INT Active Low
5V IN
6 FPC Touch I2C connector
VDD
VSH
Generic I²C Sensors
I²C Address - 0x52 RV3028 - 0x6A LSM6DSL - 0x77 BME680
KNX Nano BCU
TODO: - RV_3028 INT ist verbunden mit LORA RFM MISO. Kein gleichzeitiger Betrieb - USB ESD Diodes - Done Pin TPL5110 nicht an ESP32 IO3 verbunden - Check Cap on Mag Sensor - Remove D4 & R20
VSS
Idee: Ext Audio MAX98357 anschliessen
INT Active HIGH
VPP
JP6 abhängig von ext Netzteil einstellen
SCK
Air Q Sensor
EINK Touch Screen Connector
VGL

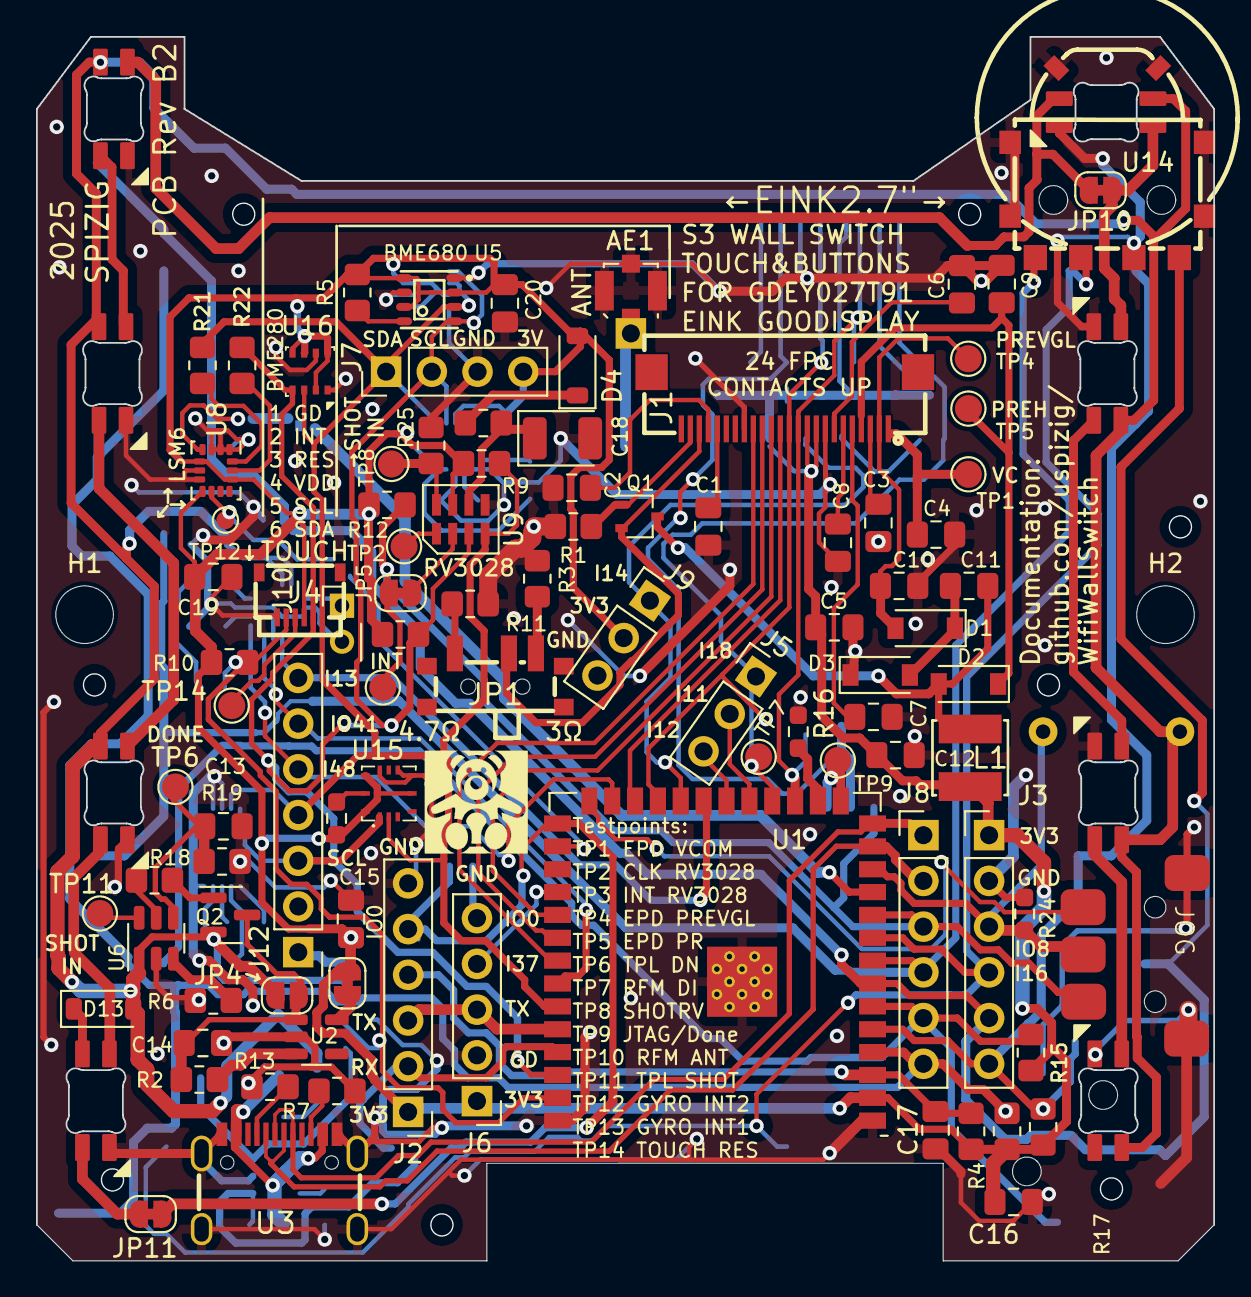
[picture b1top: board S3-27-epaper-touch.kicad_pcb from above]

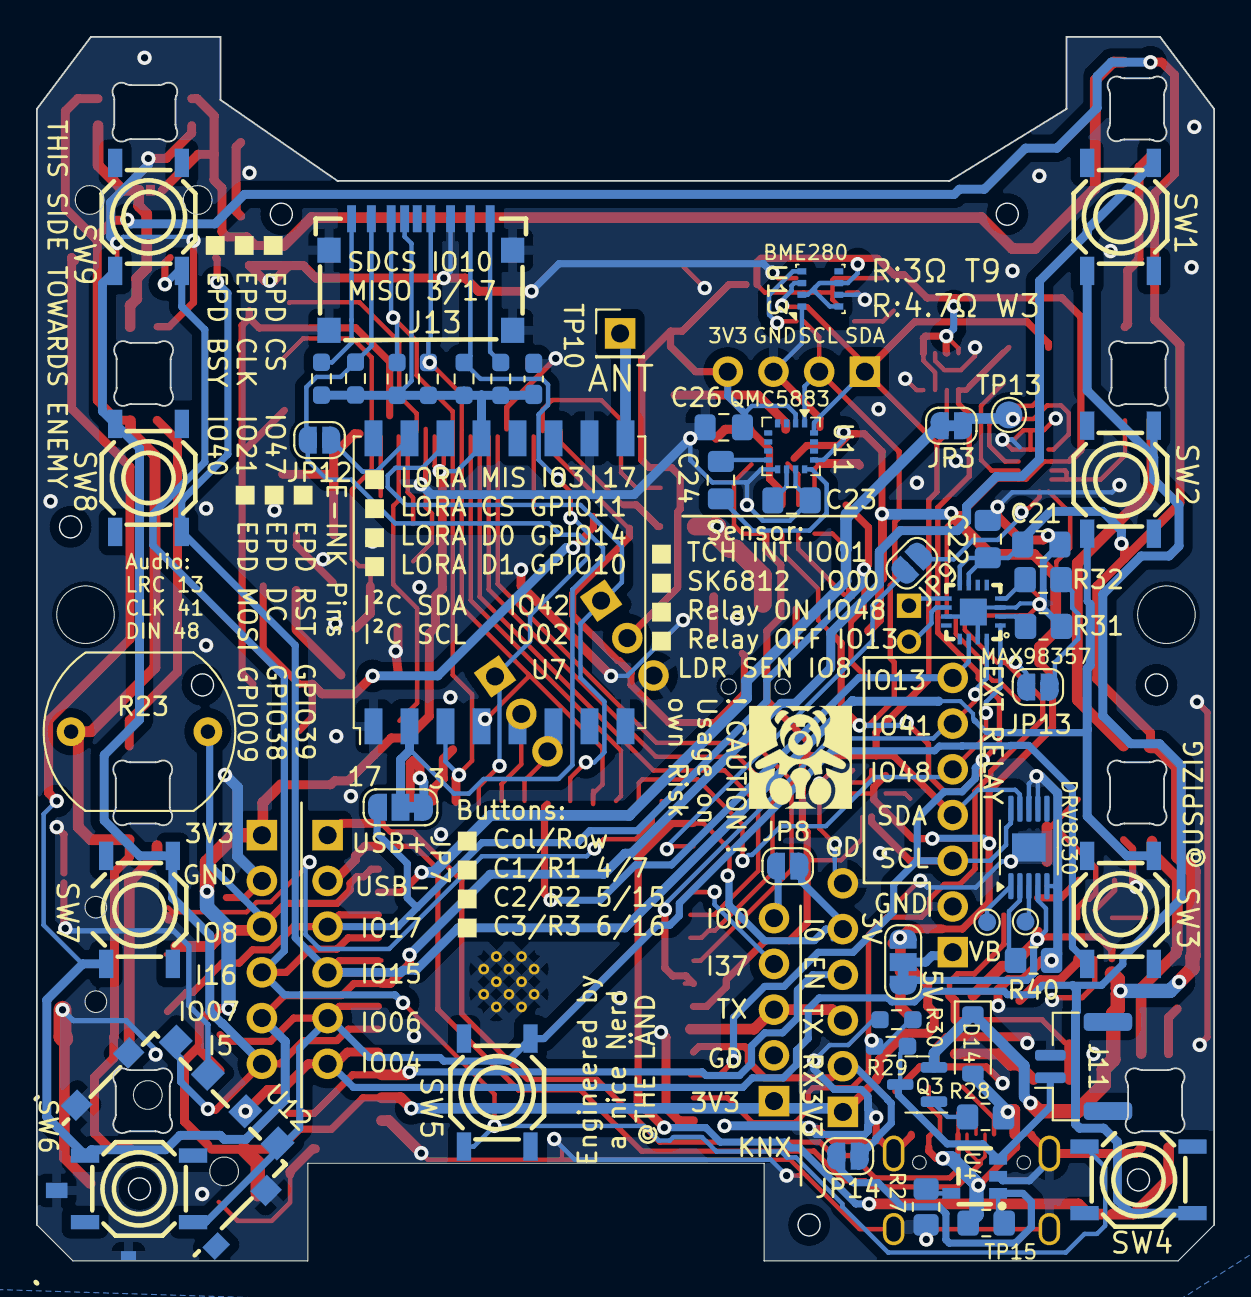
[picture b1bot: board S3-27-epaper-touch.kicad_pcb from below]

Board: 2 copper layers, 65.4 x 68.0 mm, 159 parts (62 on the bottom side), 108 nets.

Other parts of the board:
JOG: jogdial; JogWheel

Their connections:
/IO_8: JOG.2; also elsewhere on the board
/IO_17: JOG.3; also elsewhere on the board
/IO_45: JOG.1; also elsewhere on the board
GND: JOG.4; also elsewhere on the board

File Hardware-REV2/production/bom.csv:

Designator,Footprint,Quantity,Value,LCSC Part #
AE1,U.FL_Molex_MCRF_73412-0110_Vertical,1,Antenna_Shield,
"C1, C14, C15, C16, C17, C2, C3, C4, C5, C6, C7, C8",0805,12,1uF,C28323
"C10, C11, C12, C9",0805,4,4.7uF 50V_US,C162420
"C13, C19, C20",0805,3,100nF,C49678
C18,CP_EIA-3528-21_Kemet-B,1,220uF,
"C21, C22, C26",0805,3,100nF,
C23,0805,1,4u7F,
C24,0805,1,220nF,
C25,0603,1,100nF,
"D1, D13, D14, D2, D3, D4",D_SOD-123,6,MBR0530,
"D10, D11, D12, D5, D6, D7, D8, D9",MX_SK6812MINI-E,8,SK6812MINI-E,
"H1, H2",MountingHole_3.2mm_M3,2,MountingSwitch,
J1,FPC-SMD_P0.50-24P_QCHF-SM-H2.0,1,AFC24-S24FIC-00,C262292
J10,PinHeader_1x02_P2.00mm_Vertical,1,Conn_01x02_Pin,
J11,JST_GH_SM02B-GHS-TB_1x02-1MP_P1.25mm_Horizontal,1,Conn_01x02_Pin,
J12,PinHeader_1x07_P2.54mm_Vertical,1,Conn_01x07_Pin,
J13,TF-SMD_XKTF-0803-0,1,Micro_SD_Card_Det_US,
"J2, J3, J8",PinHeader_1x06_P2.54mm_Vertical,3,Conn_01x06,
J4,FFC-SMD_6P-P0.50_FH34SRJ-6S-0.5SH,1,TochConn,C224194
"J5, J9",PinHeader_1x03_P2.54mm_Vertical,2,Conn_01x03_Pin,
J6,PinHeader_1x05_P2.54mm_Vertical,1,Conn_01x05_Pin,
J7,PinHeader_1x04_P2.54mm_Vertical,1,Conn_01x04_Pin,
JOG,JogWheel,1,jogdial,
JP1,SW-SMD_G-SWITCH_MK-12C02-G015,1,RESE,C2911519
JP10,SolderJumper-2_P1.3mm_Bridged_RoundedPad1.0x1.5mm,1,Jumper_2_Open,
"JP11, JP2, JP3, JP5",SolderJumper-2_P1.3mm_Bridged_RoundedPad1.0x1.5mm,4,Jumper_2_Bridged,
"JP12, JP14, JP4, JP8",SolderJumper-2_P1.3mm_Open_RoundedPad1.0x1.5mm,4,Jumper_2_Open,
"JP13, JP9",SolderJumper-2_P1.3mm_Open_RoundedPad1.0x1.5mm,2,Jumper_2_Bridged,
"JP6, JP7",SolderJumper-3_P1.3mm_Bridged12_RoundedPad1.0x1.5mm_NumberLabels,2,Jumper_3_Bridged12,
L1,IND-SMD_L4.0-W4.0,1,10uH,
Q1,SOT-323_SC-70,1,Si1308,
"Q2, Q3",SOT-23,2,Si2301,
"R1, R10, R12, R14, R15, R17, R18, R19, R2, R25, R28, R4, R5, R8, R9",0805,15,10K,C17414
"R11, R40",0805,2,0.47R,
"R13, R27, R7",0805,3,5k11,C27834
"R16, R24, R29, R30",0603,4,N.C.,
R20,0805,1,N.C.,
"R21, R22",0805,2,0R,C17477
R23,R_LDR_10x8.5mm_P7.6mm_Vertical,1,LDR03,
R26,0805,1,800K,
R3,0805,1,3R,
R31,0805,1,100K,
R32,0805,1,330k,
R33,0603,1,100K,
"R34, R35, R36, R37, R38, R39",0603,6,10k,
R6,0805,1,220K,
"SW1, SW2, SW3, SW4, SW5, SW6, SW7, SW8, SW9",SW-SMD_4P-CORR-L5.2-W5.2-P3.70-LS6.4,9,SW_Push,
"TP1, TP13, TP7, TP9",TestPoint_Pad_D1.5mm,4,VCOM,
TP10,PinHeader_1x01_P2.54mm_Vertical,1,VCOM,
TP11,TestPoint_Pad_D1.5mm,1,SHOT,
TP12,TestPoint_Pad_D1.0mm,1,VCOM,
TP14,TestPoint_Pad_D1.5mm,1,RESET_TOUCH,
TP15,TestPoint_Pad_D1.0mm,1,M-,
TP16,TestPoint_Pad_D1.0mm,1,M+,
TP2,TestPoint_Pad_D1.5mm,1,CLKOUT,
TP3,TestPoint_Pad_D1.5mm,1,SHOT1,
TP4,TestPoint_Pad_D1.5mm,1,PREVGL,
TP5,TestPoint_Pad_D1.5mm,1,PREVGH,
TP6,TestPoint_Pad_D1.5mm,1,DONE,
TP8,TestPoint_Pad_D1.5mm,1,SHOT IN,
U1,ESP32-S3-WROOM-1,1,ESP32-S3-WROOM-1-N8,
U10,TQFN-16_L3.0-W3.0-P0.50-BL-EP1.5,1,MAX98357,
U11,LGA-16_3x3mm_P0.5mm,1,MMC5883MA,
"U12, U14",SW-SMD_SIQ-02FVS3_1,2,SIQ-02FVS3,
"U13, U16",Bosch_LGA-8_2.5x2.5mm_P0.65mm_ClockwisePinNumbering,2,BME280,
U15,ZMOD4410AI1V,1,4410AI1V,
U17,HVSSOP-10-1EP_3x3mm_P0.5mm_EP1.57x1.88mm,1,DRV8830DGQR,
U2,SOT-23-5,1,RT9013,C47773
U3,USB-C_SMD-TYPE-C-31-M-12,1,KoreanHropartsElecTYPE-C-31-M-12,C165948
U4,SOT-23-5_L3.0-W1.7-P0.95-LS2.8-BR,1,TP4065,C113540
U5,LGA-8_L3.0-W3.0-P0.80-TR,1,BME680,C125972
U6,SOT-23-6,1,TPL5110,C125830
U7,HOPERF_RFM9XW_SMD,1,RFM95W-868S2,C2844472
U8,LGA-14_3x2.5mm_P0.5mm_LayoutBorder3x4y,1,LSM6DSOWTR, C2829074
U9,rv3028,1,RV3032,

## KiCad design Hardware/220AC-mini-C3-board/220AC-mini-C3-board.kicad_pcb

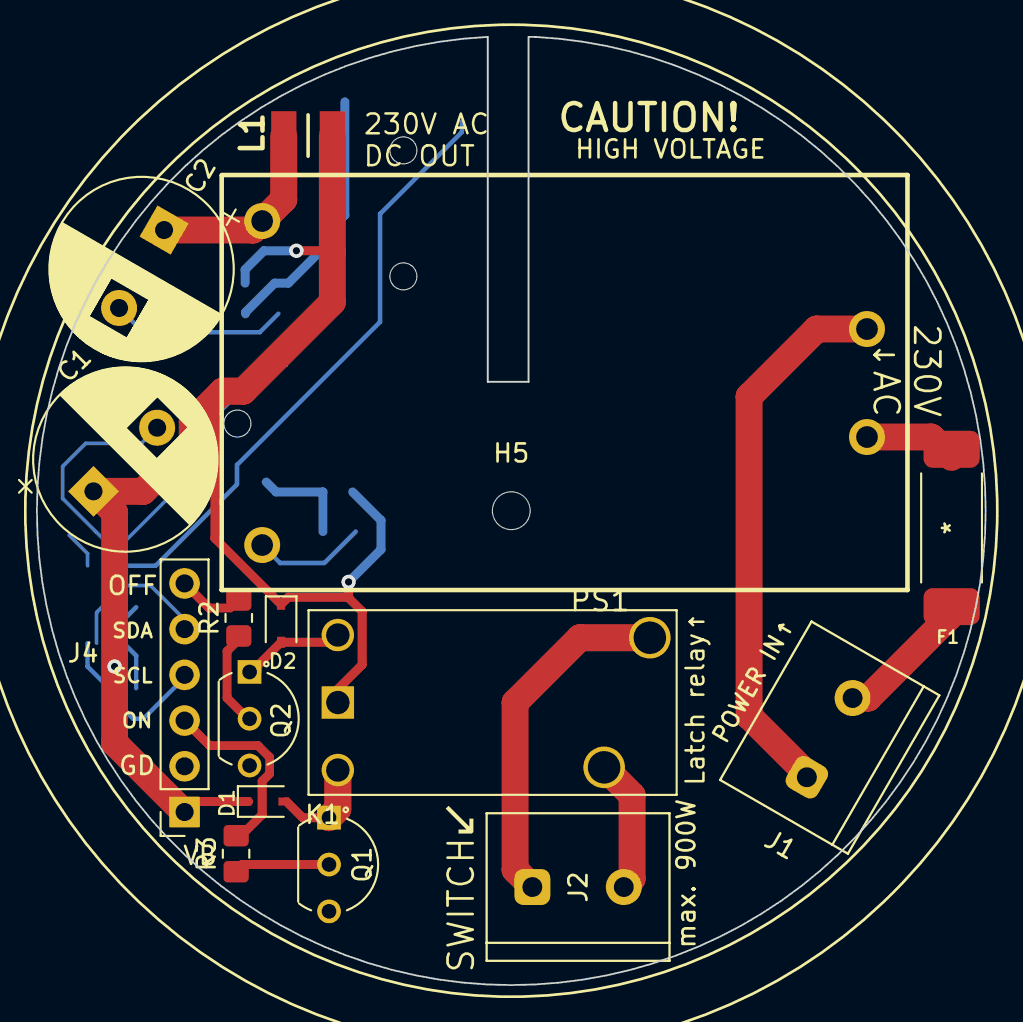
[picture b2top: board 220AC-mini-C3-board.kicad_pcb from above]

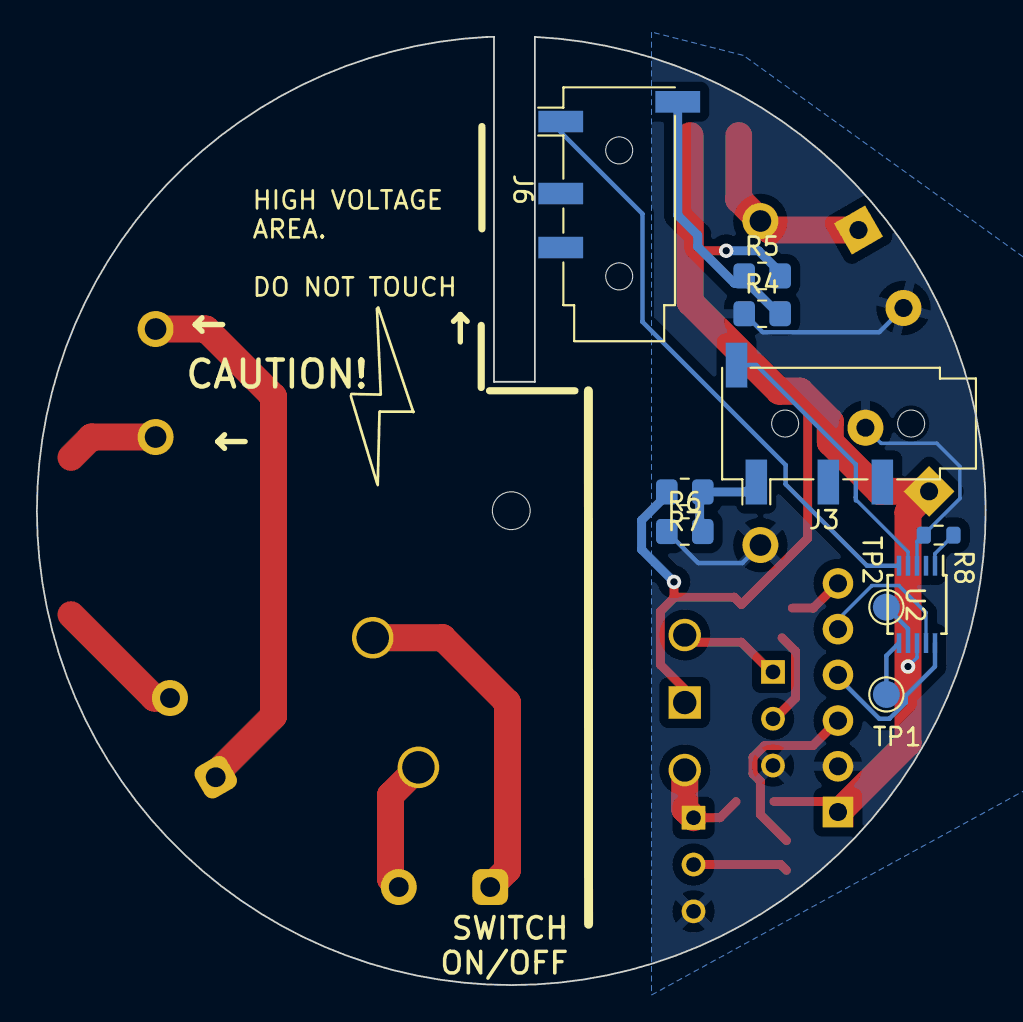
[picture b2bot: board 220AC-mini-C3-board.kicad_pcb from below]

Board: 2 copper layers, 52.7 x 52.7 mm, 26 parts (10 on the bottom side), 23 nets.

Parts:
C1, C2: 470uF; CP_Radial_D10.0mm_P5.00mm
D1, D2: 1N4148; D_SOD-323
F1: Fuse; 0443001.DR
H5: MountingHole; MountingHole_2.1mm
J1: AC MAINS POWER; Conn_C8269
J2: ON/OFF switch; Conn_C8269
J3, J6: AudioJack4; Jack_3.5mm_PJ320D_Horizontal
J4: Conn_01x06_Pin; PinSocket_1x06_P2.54mm_Vertical
K1: HF163-F; FH44L-1AT-L2-DC3V
L1: L; IND_BRL3225T4R7M
PS1: HLK-PM03; PWRM-TH_HLK-5M05
Q1, Q2: Q_NPN_CBE; BC547B
R2, R3, R4, R5, R6, R7: 430Ω; R_0805_2012Metric_Pad1.20x1.40mm_HandSolder
R8: 19k; R_0603_1608Metric
TP1, TP2: TestPoint; TestPoint_Pad_D1.5mm
U2: ADS1115IDGS; TSSOP-10_3x3mm_P0.5mm

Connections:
+3V3: C1.1, D1.1 (K), D2.1 (K), J4.1, K1.2, L1.2, R5.2, R7.2, U2.8 (VDD)
/AC (L): F1.1, J1.2
/AC (N): J1.1, PS1.2 (AC/N)
/RELAIS_OFF: J4.6, R2.2
/RELAIS_ON: J4.3, R3.2
/SCL: J4.4, U2.10 (SCL)
/SDA: J4.5, U2.9 (SDA)
GND: C1.2, C2.2, J4.2, PS1.3 (-Vout), Q1.3 (E), Q2.3 (E), R4.1, R6.1, R8.2, U2.3 (GND)
unnamed: D1.2 (A), K1.1, Q1.1 (C)
unnamed: D2.2 (A), K1.3, Q2.1 (C)
unnamed: J2.1, K1.4
unnamed: J2.2, K1.5
unnamed: J3.T, R6.2, R7.1
unnamed: J6.S, R4.2, R5.1
unnamed: C2.1, L1.1, PS1.4 (+Vout)
unnamed: F1.2, PS1.1 (AC/L)
unnamed: Q1.2 (B), R3.1
unnamed: Q2.2 (B), R2.1
unnamed: R8.1, U2.1 (ADDR)
unnamed: J3.S, U2.4 (AIN0)
unnamed: J6.T, U2.5 (AIN1)
unnamed: TP1.1, U2.6 (AIN2)
unnamed: TP2.1, U2.7 (AIN3)

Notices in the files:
Hardware-REV2/S3-27-epaper-touch.kicad_sch:
NO Comercial USE. GPL LICENSE
parts and their libraries:
Copyright 2021 Accelerated Designs. All rights reserved.
